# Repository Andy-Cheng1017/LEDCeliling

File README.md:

# LEDCeliling
 NTUT IXD Graduate Exhibition

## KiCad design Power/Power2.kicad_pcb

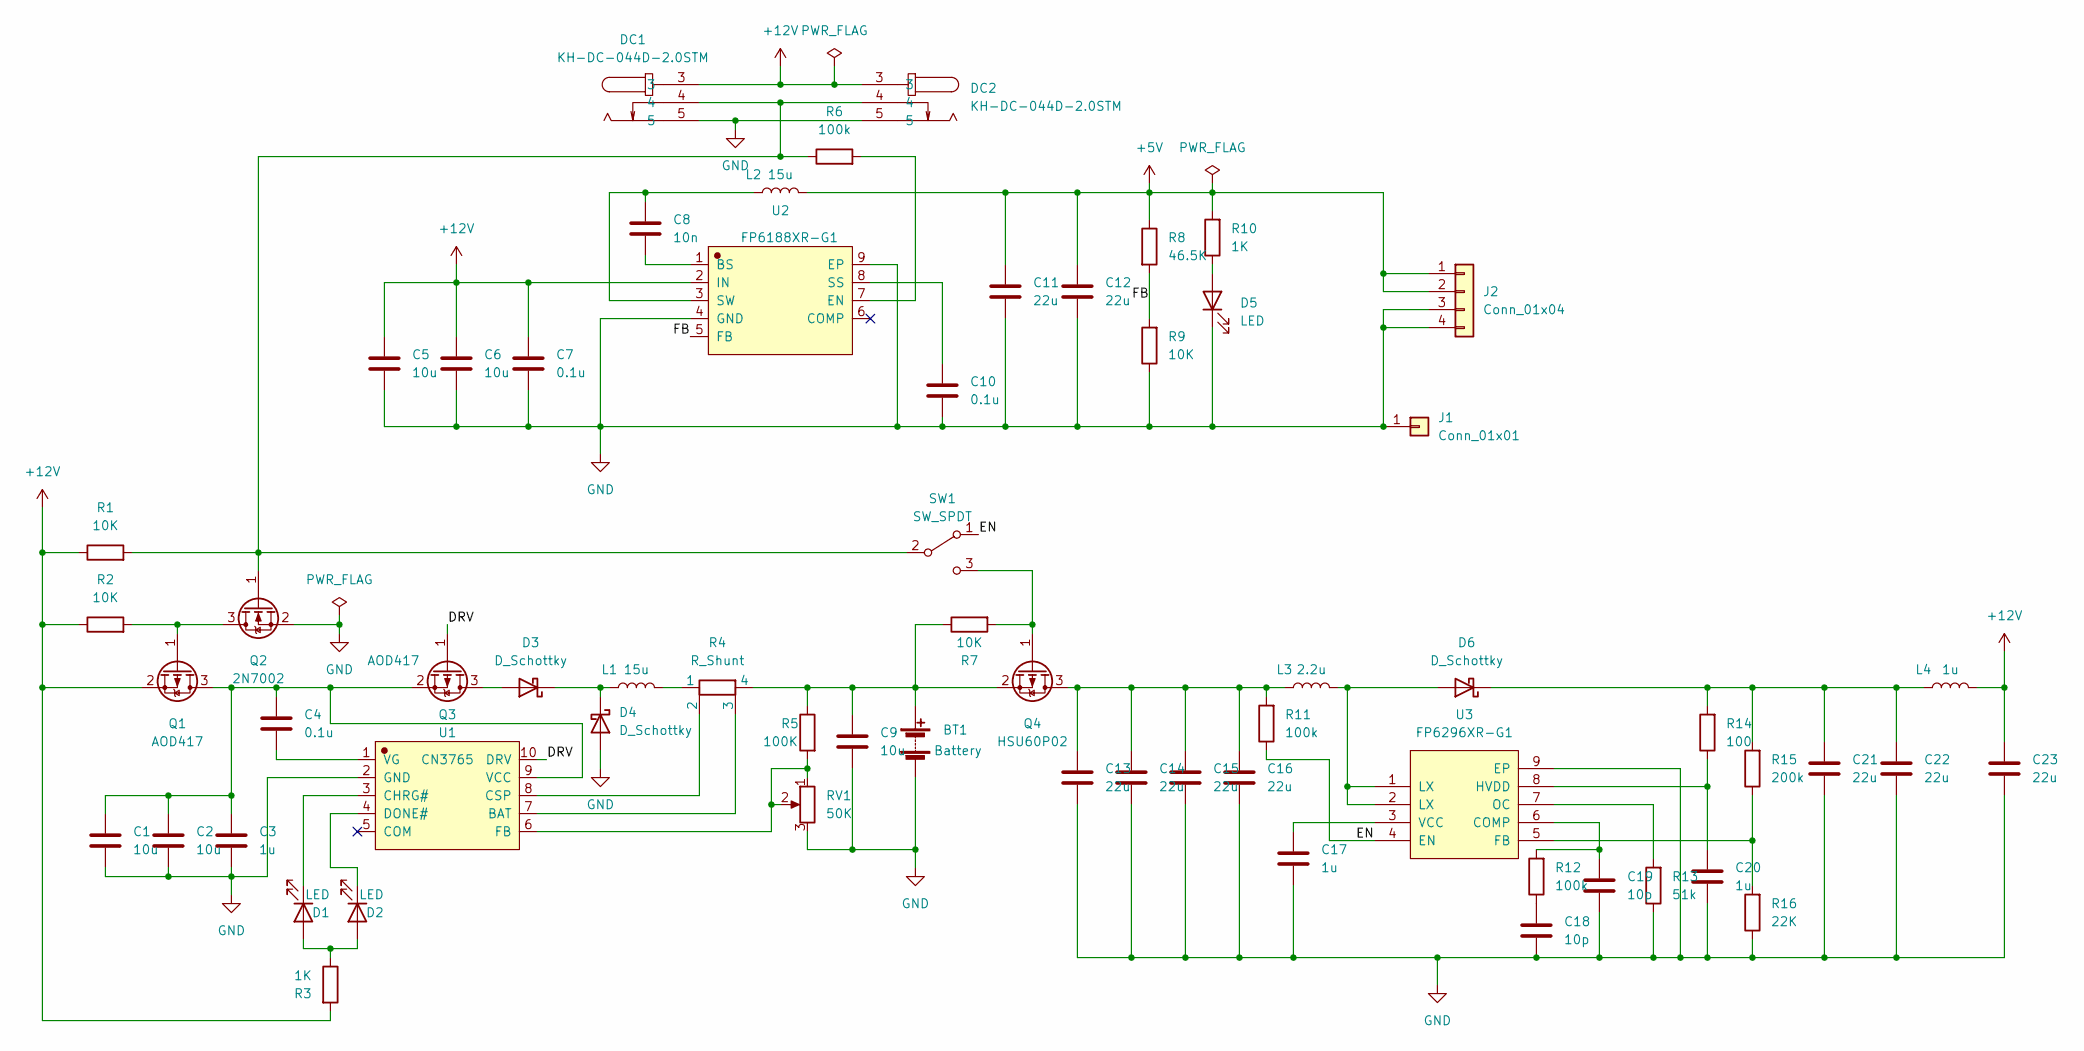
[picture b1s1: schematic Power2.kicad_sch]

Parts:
BT1: Battery
C1, C2, C5, C6, C9: 10u; C_0805_2012Metric
C3, C17, C20: 1u; C_0805_2012Metric
C4, C7, C10: 0.1u; C_0805_2012Metric
C8: 10n; C_0805_2012Metric
C11, C12, C13, C14, C15, C16, C21, C22, C23: 22u; C_0805_2012Metric
C18, C19: 10p; C_0805_2012Metric
D1, D2, D5: LED; LED_0805_2012Metric
D3, D4: D_Schottky; D_SMA
D6: D_Schottky; D_SMB
DC1, DC2: KH-DC-044D-2.0STM; DC-IN-TH_KH-DC-044D-2.0STM
J1: Conn_01x01; GndConnect
J2: Conn_01x04; VH3.96 4P SMT
L1, L2: 15u; IND-SMD_L7.5-W6.6
L3: 2.2u; IND-SMD_L7.5-W6.6
L4: 1u; L_1008_2520Metric
Q1, Q3: AOD417; TO-252-2
Q2: 2N7002; SOT-23
Q4: HSU60P02; TO-252-2
R1, R2, R7, R9: 10K; R_0805_2012Metric
R3, R10: 1K; R_0805_2012Metric
R4: R_Shunt; R_2512_6332Metric
R5: 100K; R_0805_2012Metric
R6, R11, R12: 100k; R_0805_2012Metric
R8: 46.5K; R_0805_2012Metric
R13: 51k; R_0805_2012Metric
R14: 100; R_0805_2012Metric
R15: 200k; R_0805_2012Metric
R16: 22K; R_0805_2012Metric
RV1: 50K; Potentiometer_Bourns_TC33X_Vertical
SW1: SW_SPDT; SW_SPDT_PCM12
U1: CN3765; SOIC-10_L4.9-W3.9-P1.00-LS6.0-BL
U2: FP6188XR-G1; SOIC-8-1EP_3.9x4.9mm_P1.27mm_EP2.95x4.9mm_Mask2.71x3.4mm_Th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
U3: FP6296XR-G1; SOIC-8-1EP_3.9x4.9mm_P1.27mm_EP2.95x4.9mm_Mask2.71x3.4mm_Th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

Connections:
+5V: C11.1, C12.1, J2.1, J2.2, L2.2, R8.1, R10.2
+12V: C5.1, C6.1, C7.1, C23.1, DC1.3, DC2.3, L4.2, Q1.2 (S), R1.1, R2.1, R3.2, U2.2 (IN)
/DRV: Q3.1 (G), U1.10 (DRV)
/EN: R11.1, SW1.1 (A), U3.4 (EN)
/FB: R8.2, R9.2, U2.5 (FB)
GND: BT1.2 (-), C1.2, C2.2, C3.2, C5.2, C6.2, C7.2, C9.2, C10.2, C11.2, C12.2, C13.2, C14.2, C15.2, C16.2, C17.2, C18.2, C19.2, C20.2, C21.2, C22.2, C23.2, D4.2 (A), D5.1 (K), DC1.5, DC2.5, J1.1, J2.3, J2.4, Q2.2 (S), R9.1, R13.1, R16.1, RV1.3, U1.2 (GND), U2.4 (GND), U2.9 (EP), U3.9 (EP)
unnamed: BT1.1 (+), C9.1, Q4.2 (S), R4.4, R5.1, R7.1
unnamed: C1.1, C2.1, C3.1, C4.1, Q1.3 (D), Q3.2 (S), U1.9 (VCC)
unnamed: C4.2, U1.1 (VG)
unnamed: C8.1, U2.1 (BS)
unnamed: C8.2, L2.1, U2.3 (SW)
unnamed: C10.1, U2.8 (SS)
unnamed: C13.1, C14.1, C15.1, C16.1, L3.1, Q4.3 (D), R11.2
unnamed: C17.1, U3.3 (VCC)
unnamed: C18.1, R12.1
unnamed: C19.1, R12.2, U3.6 (COMP)
unnamed: C20.1, R14.1, U3.8 (HVDD)
unnamed: C21.1, C22.1, D6.1 (K), L4.1, R14.2, R15.2
unnamed: D1.1 (K), U1.3 (CHRG#)
unnamed: D1.2 (A), D2.2 (A), R3.1
unnamed: D2.1 (K), U1.4 (DONE#)
unnamed: D3.1 (K), D4.1 (K), L1.1
unnamed: D3.2 (A), Q3.3 (D)
unnamed: D5.2 (A), R10.1
unnamed: D6.2 (A), L3.2, U3.1 (LX), U3.2 (LX)
unnamed: DC1.4, DC2.4, Q2.1 (G), R1.2, R6.1, SW1.2 (B)
unnamed: L1.2, R4.1
unnamed: Q1.1 (G), Q2.3 (D), R2.2
unnamed: Q4.1 (G), R7.2, SW1.3 (C)
unnamed: R4.2, U1.8 (CSP)
unnamed: R4.3, U1.7 (BAT)
unnamed: R5.2, RV1.1, RV1.2, U1.6 (FB)
unnamed: R6.2, U2.7 (EN)
unnamed: R13.2, U3.7 (OC)
unnamed: R15.1, R16.2, U3.5 (FB)

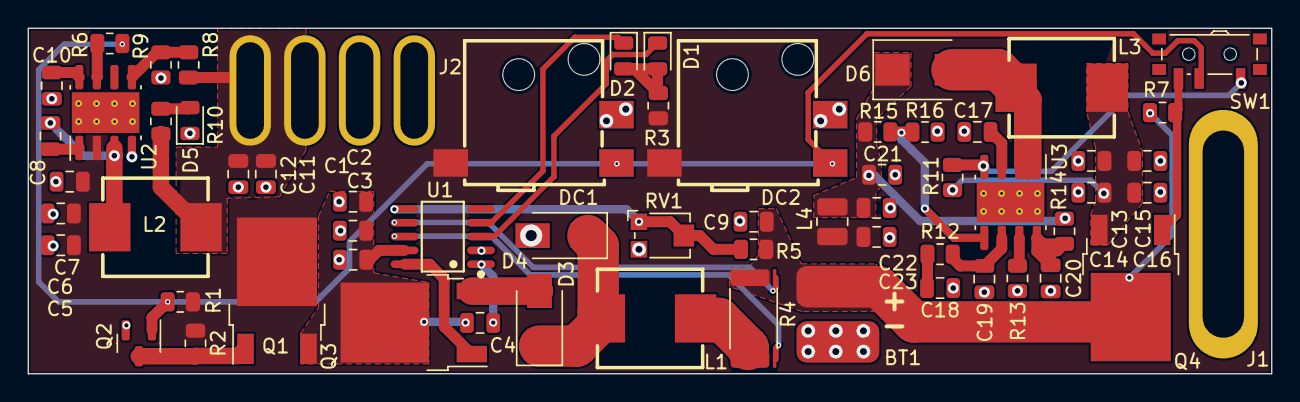
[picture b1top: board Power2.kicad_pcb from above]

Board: 2 copper layers, 90.0 x 25.0 mm, 63 parts (0 on the bottom side), 35 nets.

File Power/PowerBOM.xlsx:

Comment | Designator | Footprint | JLCPCB Part
10u | C1, C2, C5, C6, C9, | Capacitor_SMD:C_0805_2012Metric | C15850
1u | C3, C17, C20, | Capacitor_SMD:C_0805_2012Metric | C2798196
0.1u | C4, C7, C10, | Capacitor_SMD:C_0805_2012Metric | C282732
10n | C8, | Capacitor_SMD:C_0805_2012Metric | C376921
22u | C11, C12, C13, C14, C15, C16, C21, C22, C23, | Capacitor_SMD:C_0805_2012Metric | C45783
10p | C18, C19, | Capacitor_SMD:C_0805_2012Metric | C344177
LED | D1, D5, | LED_SMD:LED_0805_2012Metric | C965812
LED | D2 | LED_SMD:LED_0805_2012Metric | C965816
D_Schottky | D3, D4, | Diode_SMD:D_SMA | C3018536
D_Schottky | D6, | Diode_SMD:D_SMB | C2903947
KH-DC-044D-2.0STM | DC1, DC2, | 1component:DC-044D-2.5A-2.5-SMT | C397343
15u | L1, L2, | 1component:IND-SMD_L7.5-W6.6 | C3002651
2.2u | L3, | 1component:IND-SMD_L7.5-W6.6 | C3002634
1u | L4, | Inductor_SMD:L_1008_2520Metric | C2044935
AOD417 | Q1, Q3, | Package_TO_SOT_SMD:TO-252-2 | C4748754
2N7002 | Q2, | Package_TO_SOT_SMD:SOT-23 | C3008370
HSU60P02 | Q4, | Package_TO_SOT_SMD:TO-252-2 | C845610
10K | R1, R2, R7, R9, | Resistor_SMD:R_0805_2012Metric | C3152217
1K | R3, R10, | Resistor_SMD:R_0805_2012Metric | C17414
100k | R5, R6, R11, R12, | Resistor_SMD:R_0805_2012Metric | C149504
46.5K | R8, | Resistor_SMD:R_0805_2012Metric | C17704
51k | R13, | Resistor_SMD:R_0805_2012Metric | C5356361
100 | R14, | Resistor_SMD:R_0805_2012Metric | C25277
200k | R15, | Resistor_SMD:R_0805_2012Metric | C5356338
22K | R16, | Resistor_SMD:R_0805_2012Metric | C5140879
50K | RV1, | 1component:Potentiometer_Bourns_TC33X_Vertical | C145161
SW_SPDT | SW1, | Button_Switch_SMD:SW_SPDT_PCM12 | C431540
CN3765 | U1, | 1component:SOIC-10_L4.9-W3.9-P1.00-LS6.0-BL | C41308
FP6188XR-G1 | U2, | 1component:SOIC-8-1EP_3.9x4.9mm_P1.27mm_EP2.95x4.9mm_Mask2.71x3.4mm_ThermalVias | C114311
FP6296XR-G1 | U3, | 1component:SOIC-8-1EP_3.9x4.9mm_P1.27mm_EP2.95x4.9mm_Mask2.71x3.4mm_ThermalVias | C133888

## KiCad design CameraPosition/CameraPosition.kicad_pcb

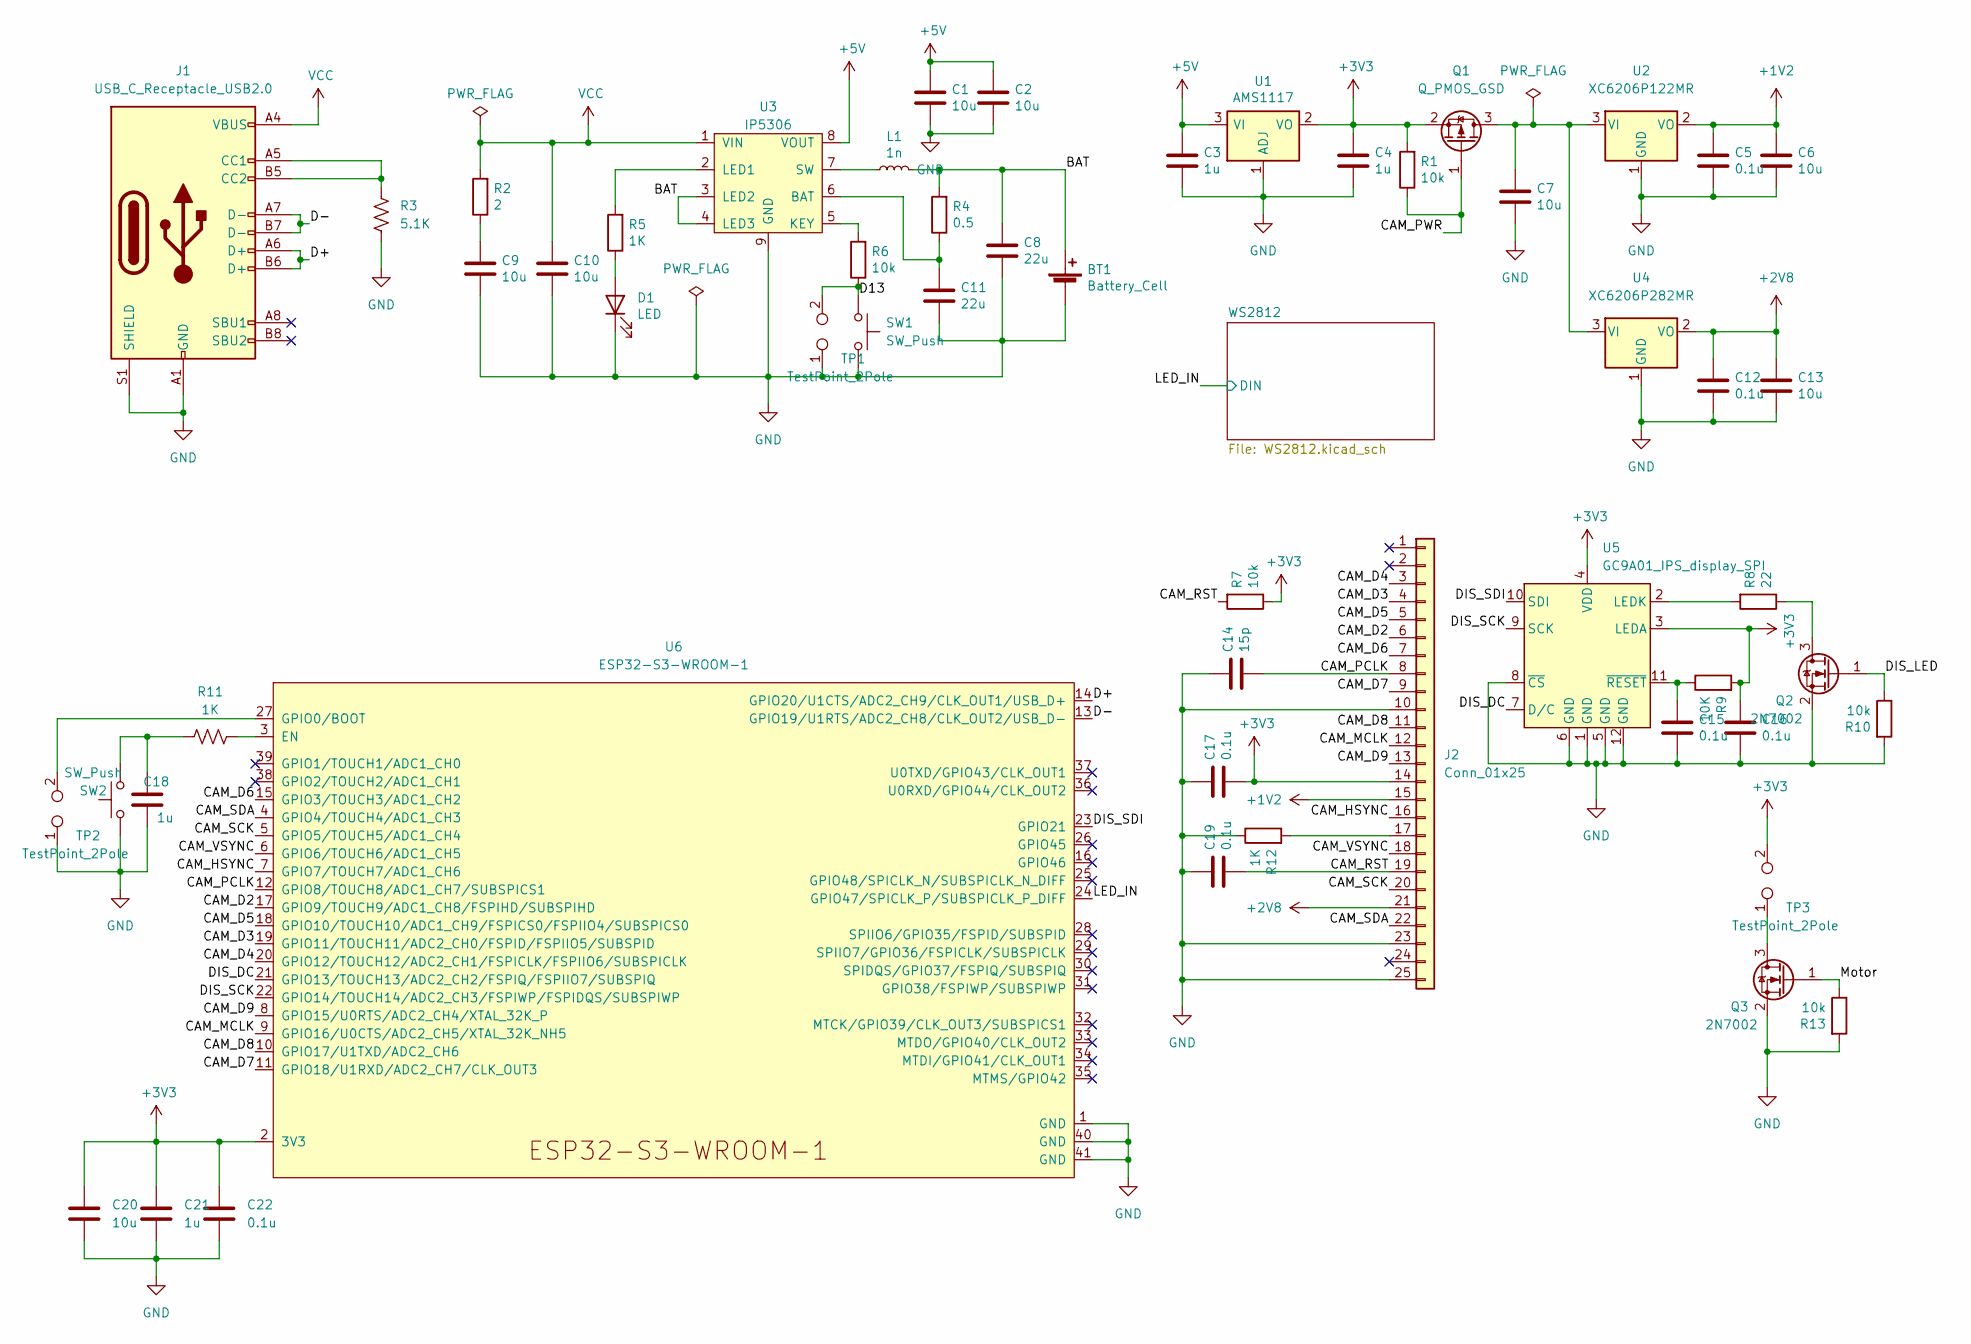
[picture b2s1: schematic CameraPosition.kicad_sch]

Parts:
BT1: Battery_Cell; PinHeader_1x02_P2.54mm_Vertical
C1, C2, C6, C7, C9, C10, C13, C20: 10u; C_0805_2012Metric
C3, C4, C18, C21: 1u; C_0805_2012Metric
C5, C12, C15, C16, C17, C19, C22: 0.1u; C_0805_2012Metric
C8, C11: 22u; C_0805_2012Metric
C14: 15p; C_0805_2012Metric
D1: LED; LED_0805_2012Metric
J1: USB_C_Receptacle_USB2.0; USB_C_Receptacle_HRO_TYPE-C-31-M-12
J2: Conn_01x25; Hirose_FH12-24S-0.5SH_1x24-1MP_P0.50mm_Horizontal
L1: 1n; L_Wuerth_MAPI-2512
Q1: Q_PMOS_GSD; SOT-23
Q2, Q3: 2N7002; SOT-23
R1, R6, R7, R10, R13: 10k; R_0805_2012Metric
R2: 2; R_0805_2012Metric
R3: 5.1K; R_0805_2012Metric
R4: 0.5; R_0805_2012Metric
R5, R11, R12: 1K; R_0805_2012Metric
R8: 22; R_0805_2012Metric
R9: 10K; R_0805_2012Metric
SW1, SW2: SW_Push; SW_SPST_CK_RS282G05A3
TP1, TP2, TP3: TestPoint_2Pole; PinHeader_1x02_P2.00mm_Vertical
U1: AMS1117; SOT-223-3_TabPin2
U2: XC6206P122MR; SOT-23
U3: IP5306; SOIC-8-1EP_3.9x4.9mm_P1.27mm_EP2.29x3mm
U4: XC6206P282MR; SOT-23
U5: GC9A01_IPS_display_SPI; GC9A01_IPS_display
U6: ESP32-S3-WROOM-1; ESP32-S3-WROOM-1U

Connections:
+1V2: C5.2, C6.2, J2.15, U2.2 (VO)
+2V8: C12.2, C13.2, J2.21, U4.2 (VO)
+3V3: C4.2, C16.2, C17.1, C20.1, C21.1, C22.1, J2.14, Q1.2 (S), R1.2, R7.1, R9.2, TP3.2, U1.2 (VO), U5.3 (LEDA), U5.4 (VDD), U6.2 (3V3)
+5V: C1.2, C2.2, C3.2, U1.3 (VI), U3.8 (VOUT); also elsewhere on the board
/BAT: BT1.1 (+), C8.2, L1.2, R4.2, U3.3 (LED2), U3.4 (LED3)
/CAM_D2: J2.6, U6.17 (GPIO9/TOUCH9/ADC1_CH8/FSPIHD/SUBSPIHD)
/CAM_D3: J2.4, U6.19 (GPIO11/TOUCH11/ADC2_CH0/FSPID/FSPIIO5/S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)
/CAM_D4: J2.3, U6.20 (GPIO12/TOUCH12/ADC2_CH1/FSPICLK/FSPIIO6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)
/CAM_D5: J2.5, U6.18 (GPIO10/TOUCH10/ADC1_CH9/FSPICS0/FSPIIO4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)
/CAM_D6: J2.7, U6.15 (GPIO3/TOUCH3/ADC1_CH2)
/CAM_D7: J2.9, U6.11 (GPIO18/U1RXD/ADC2_CH7/CLK_OUT3)
/CAM_D8: J2.11, U6.10 (GPIO17/U1TXD/ADC2_CH6)
/CAM_D9: J2.13, U6.8 (GPIO15/U0RTS/ADC2_CH4/XTAL_32K_P)
/CAM_HSYNC: J2.16, U6.7 (GPIO7/TOUCH7/ADC1_CH6)
/CAM_MCLK: J2.12, U6.9 (GPIO16/U0CTS/ADC2_CH5/XTAL_32K_NH5)
/CAM_PCLK: C14.1, J2.8, U6.12 (GPIO8/TOUCH8/ADC1_CH7/SUBSPICS1)
/CAM_PWR: Q1.1 (G), R1.1
/CAM_RST: C19.1, J2.19, R7.2
/CAM_SCK: J2.20, U6.5 (GPIO5/TOUCH5/ADC1_CH4)
/CAM_SDA: J2.22, U6.4 (GPIO4/TOUCH4/ADC1_CH3)
/CAM_VSYNC: J2.18, U6.6 (GPIO6/TOUCH6/ADC1_CH5)
/D13: R6.1, SW1.1, TP1.2
/D+: J1.A6 (D+), J1.B6 (D+), U6.14 (GPIO20/U1CTS/ADC2_CH9/CLK_OUT1/USB_D+)
/D-: J1.A7 (D-), J1.B7 (D-), U6.13 (GPIO19/U1RTS/ADC2_CH8/CLK_OUT2/USB_D-)
/DIS_DC: U5.7 (D/C), U6.21 (GPIO13/TOUCH13/ADC2_CH2/FSPIQ/FSPIIO7/S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)
/DIS_LED: Q2.1 (G), R10.1
/DIS_SCK: U5.9 (SCK), U6.22 (GPIO14/TOUCH14/ADC2_CH3/FSPIWP/FSPIDQS/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)
/DIS_SDI: U5.10 (SDI), U6.23 (GPIO21)
/LED_IN: U6.24 (GPIO47/SPICLK_P/SUBSPICLK_P_DIFF); also elsewhere on the board
/Motor: Q3.1 (G), R13.1
GND: BT1.2 (-), C1.1, C2.1, C3.1, C4.1, C5.1, C6.1, C7.1, C8.1, C9.1, C10.1, C11.1, C12.1, C13.1, C14.2, C15.1, C16.1, C17.2, C18.1, C19.2, C20.2, C21.2, C22.2, D1.1 (K), J1.A1 (GND), J1.A12 (GND), J1.B1 (GND), J1.B12 (GND), J1.S1 (SHIELD), J2.10, J2.23, J2.25, Q2.2 (S), Q3.2 (S), R3.2, R10.2, R12.1, R13.2, SW1.2, SW2.1, TP1.1, TP2.1, U1.1 (ADJ), U2.1 (GND), U3.9 (GND), U4.1 (GND), U5.1 (GND), U5.5 (GND), U5.6 (GND), U5.8 (~CS), U5.12 (GND), U6.1 (GND), U6.40 (GND), U6.41 (GND); also elsewhere on the board
unnamed: C7.2, Q1.3 (D), U2.3 (VI), U4.3 (VI)
unnamed: C9.2, R2.1
unnamed: C11.2, R4.1, U3.6 (BAT)
unnamed: C15.2, R9.1, U5.11 (~RESET)
unnamed: C18.2, R11.1, SW2.2
unnamed: D1.2 (A), R5.1
unnamed: J1.A5 (CC1), J1.B5 (CC2), R3.1
unnamed: J2.17, R12.2
unnamed: L1.1, U3.7 (SW)
unnamed: Q2.3 (D), R8.1
unnamed: Q3.3 (D), TP3.1
unnamed: R5.2, U3.2 (LED1)
unnamed: R6.2, U3.5 (KEY)
unnamed: R8.2, U5.2 (LEDK)
unnamed: R11.2, U6.3 (EN)
unnamed: TP2.2, U6.27 (GPIO0/BOOT)
VCC: C10.2, J1.A4 (VBUS), J1.A9 (VBUS), J1.B4 (VBUS), J1.B9 (VBUS), R2.2, U3.1 (VIN)

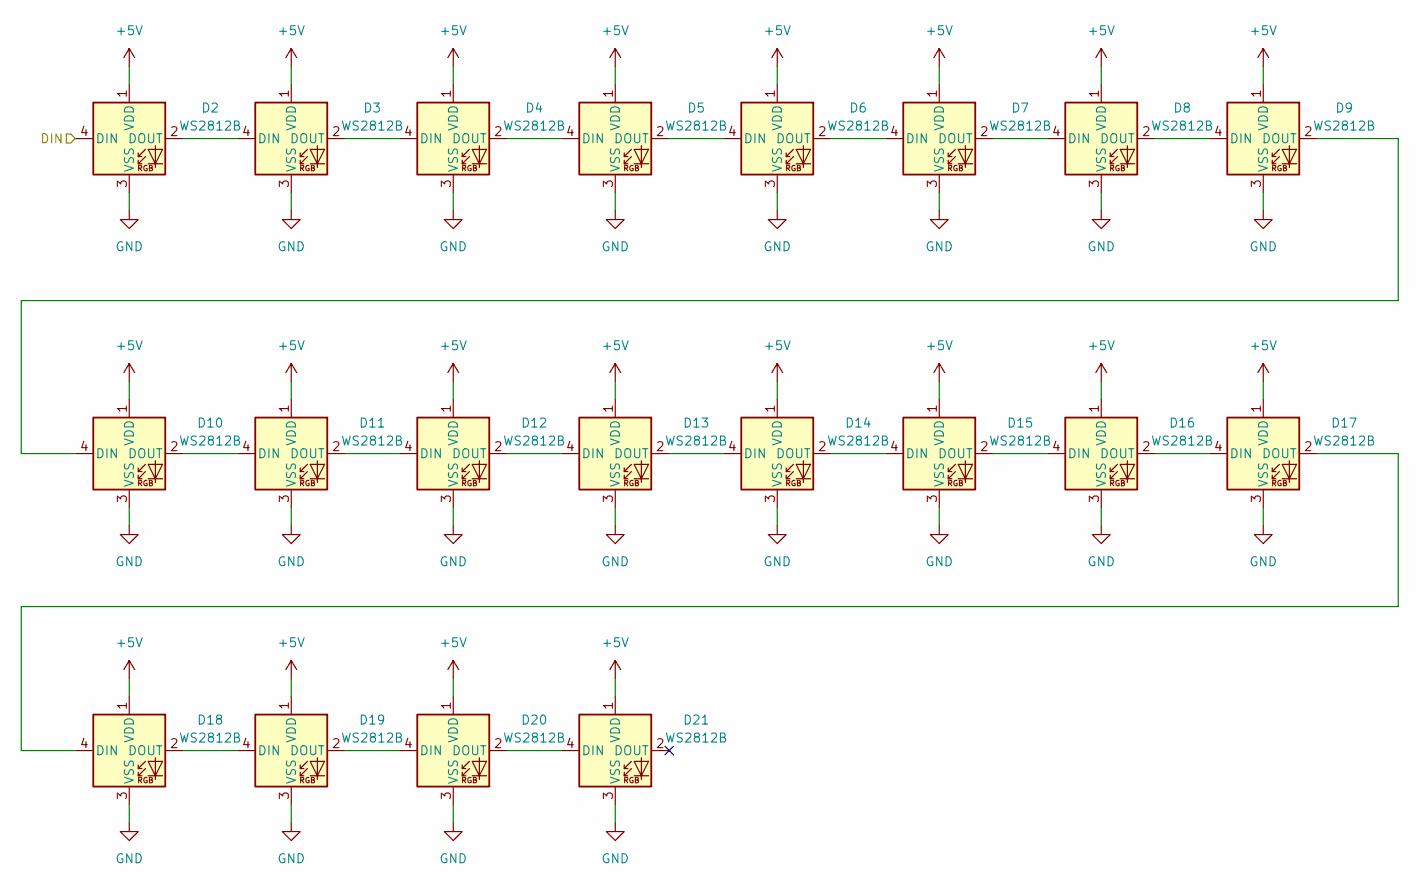
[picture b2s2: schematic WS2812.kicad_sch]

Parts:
D2, D3, D4, D5, D6, D7, D8, D9, D10, D11, D12, D13, D14, D15, D16, D17, D18, D19, D20, D21: WS2812B; LED_WS2812B_PLCC4_5.0x5.0mm_P3.2mm

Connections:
+5V: D2.1 (VDD), D3.1 (VDD), D4.1 (VDD), D5.1 (VDD), D6.1 (VDD), D7.1 (VDD), D8.1 (VDD), D9.1 (VDD), D10.1 (VDD), D11.1 (VDD), D12.1 (VDD), D13.1 (VDD), D14.1 (VDD), D15.1 (VDD), D16.1 (VDD), D17.1 (VDD), D18.1 (VDD), D19.1 (VDD), D20.1 (VDD), D21.1 (VDD); also elsewhere on the board
/LED_IN: D2.4 (DIN); also elsewhere on the board
GND: D2.3 (VSS), D3.3 (VSS), D4.3 (VSS), D5.3 (VSS), D6.3 (VSS), D7.3 (VSS), D8.3 (VSS), D9.3 (VSS), D10.3 (VSS), D11.3 (VSS), D12.3 (VSS), D13.3 (VSS), D14.3 (VSS), D15.3 (VSS), D16.3 (VSS), D17.3 (VSS), D18.3 (VSS), D19.3 (VSS), D20.3 (VSS), D21.3 (VSS); also elsewhere on the board
unnamed: D2.2 (DOUT), D3.4 (DIN)
unnamed: D3.2 (DOUT), D4.4 (DIN)
unnamed: D4.2 (DOUT), D5.4 (DIN)
unnamed: D5.2 (DOUT), D6.4 (DIN)
unnamed: D6.2 (DOUT), D7.4 (DIN)
unnamed: D7.2 (DOUT), D8.4 (DIN)
unnamed: D8.2 (DOUT), D9.4 (DIN)
unnamed: D10.2 (DOUT), D11.4 (DIN)
unnamed: D9.2 (DOUT), D10.4 (DIN)
unnamed: D11.2 (DOUT), D12.4 (DIN)
unnamed: D12.2 (DOUT), D13.4 (DIN)
unnamed: D13.2 (DOUT), D14.4 (DIN)
unnamed: D14.2 (DOUT), D15.4 (DIN)
unnamed: D15.2 (DOUT), D16.4 (DIN)
unnamed: D16.2 (DOUT), D17.4 (DIN)
unnamed: D17.2 (DOUT), D18.4 (DIN)
unnamed: D18.2 (DOUT), D19.4 (DIN)
unnamed: D19.2 (DOUT), D20.4 (DIN)
unnamed: D20.2 (DOUT), D21.4 (DIN)

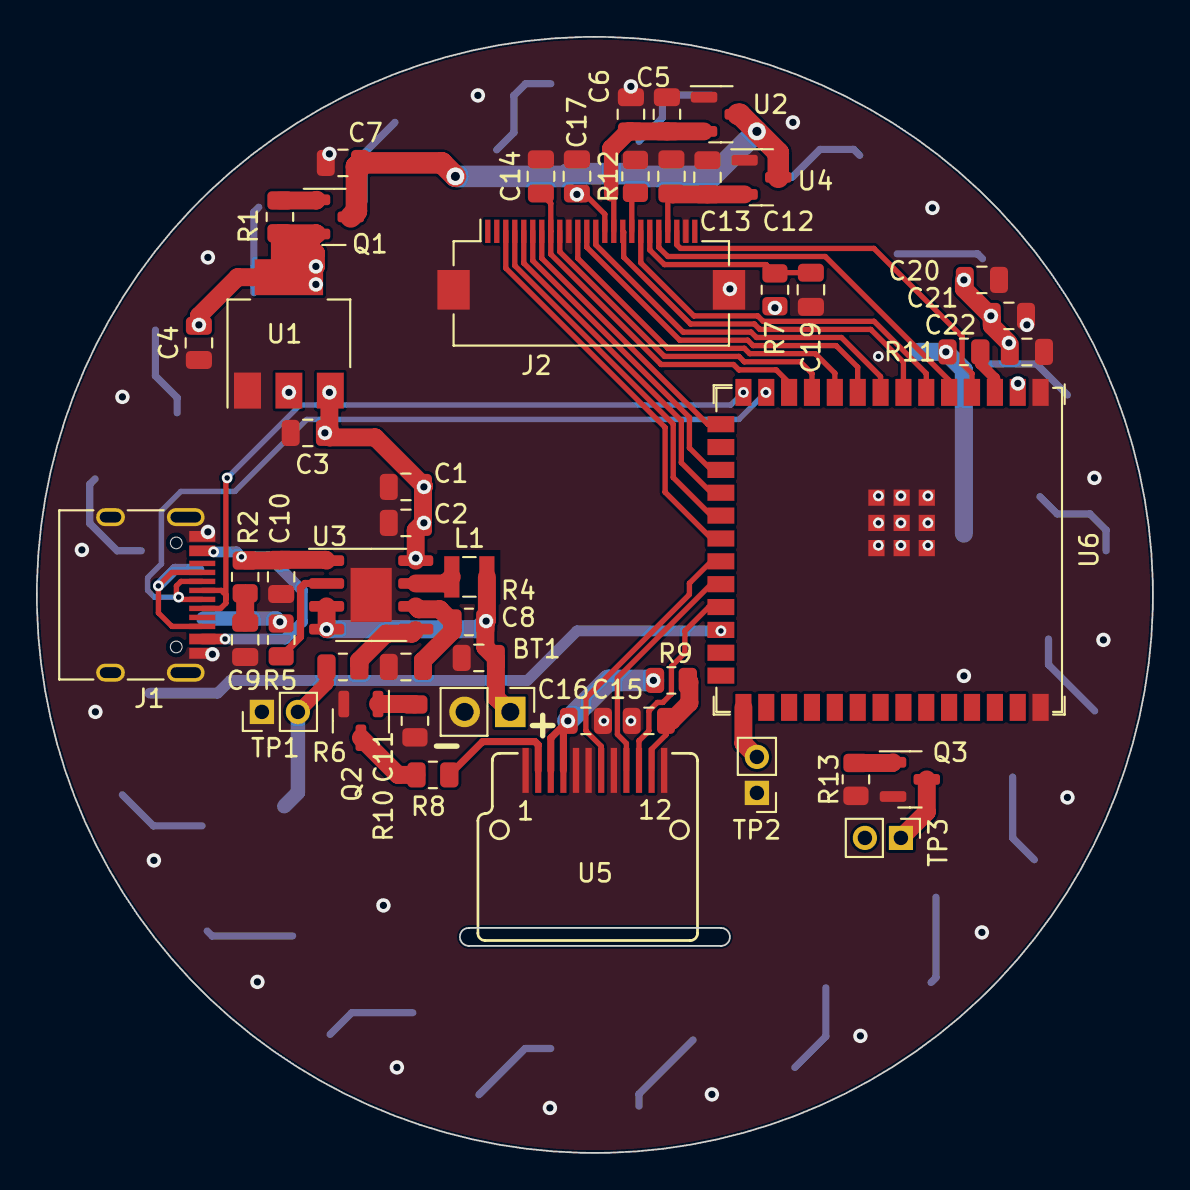
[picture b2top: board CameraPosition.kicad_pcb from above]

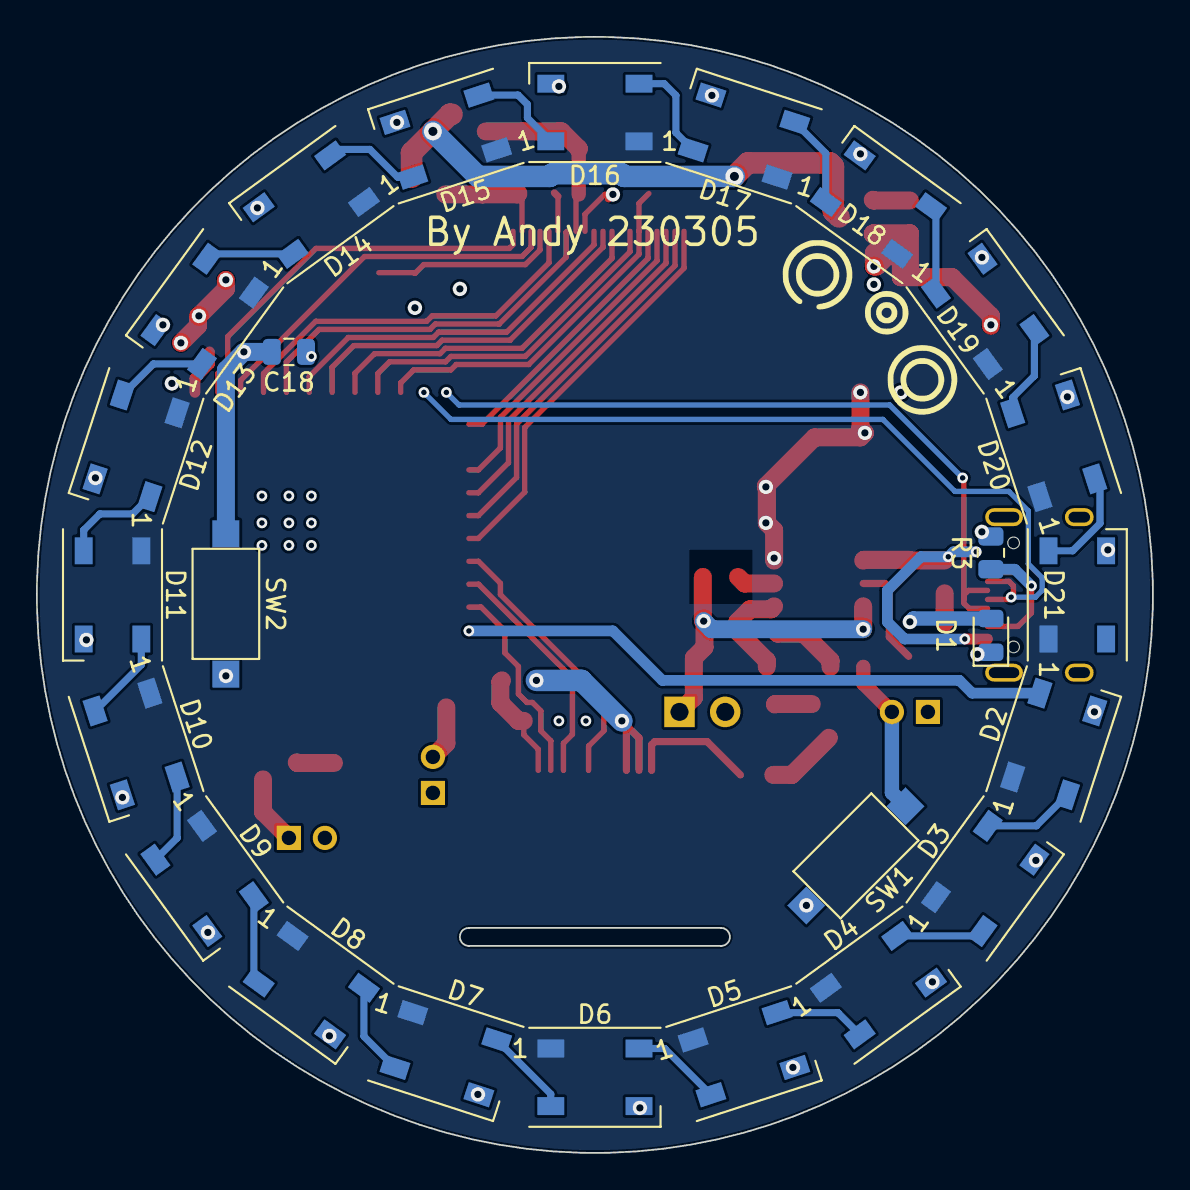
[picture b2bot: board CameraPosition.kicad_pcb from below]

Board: 4 copper layers, 62.0 x 62.0 mm, 74 parts (25 on the bottom side), 67 nets.

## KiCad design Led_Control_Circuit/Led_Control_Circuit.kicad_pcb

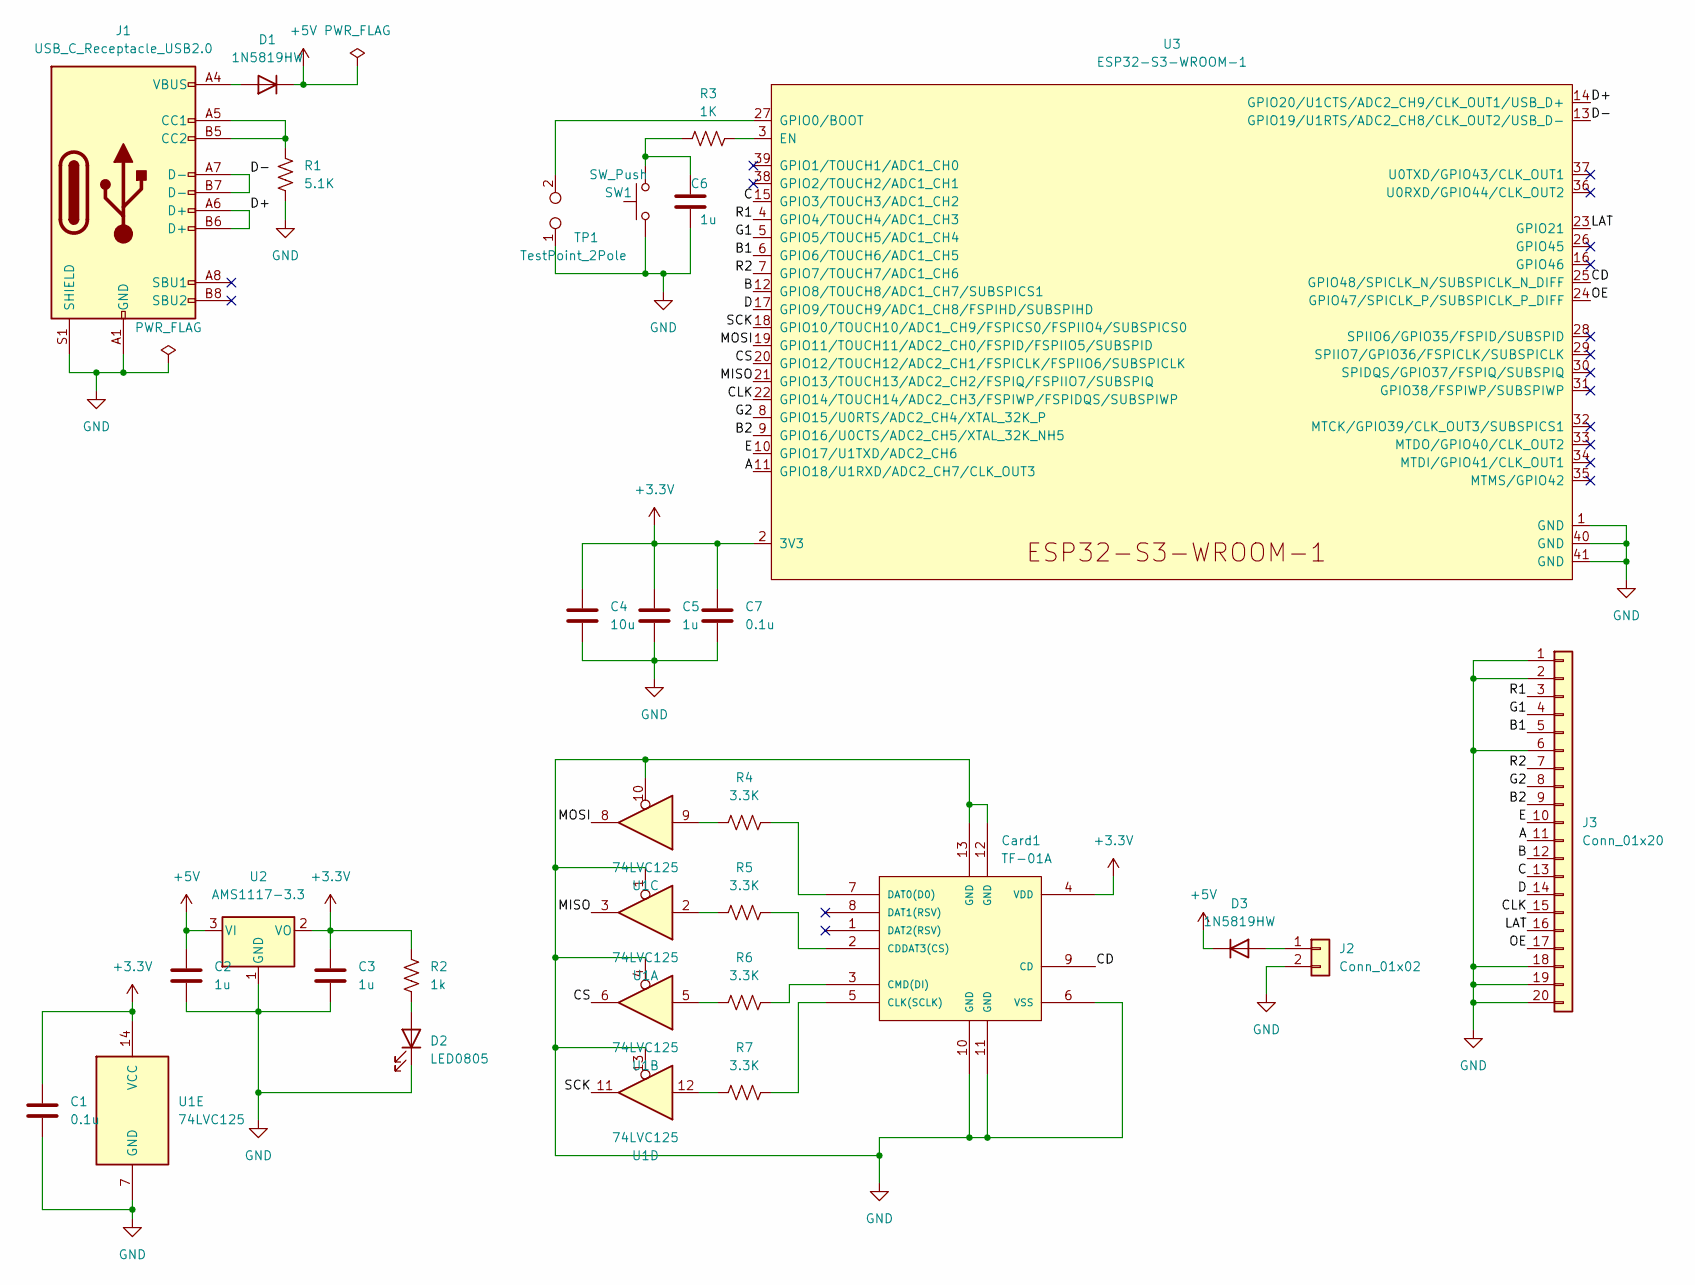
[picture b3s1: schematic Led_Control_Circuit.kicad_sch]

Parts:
C1, C7: 0.1u; C_0805_2012Metric
C2, C3, C5, C6: 1u; C_0805_2012Metric
C4: 10u; C_0805_2012Metric
Card1: TF-01A; TF-SMD_TF-01A
D1, D3: 1N5819HW; D_SOD-123
D2: LED0805; LED_0805_2012Metric
J1: USB_C_Receptacle_USB2.0; USB_C_Receptacle_HRO_TYPE-C-31-M-12
J2: Conn_01x02; Battery
J3: Conn_01x20; PinSocket_2x10_P2.54mm_Vertical_SMD
R1: 5.1K; R_0805_2012Metric
R2: 1k; R_0805_2012Metric
R3: 1K; R_0805_2012Metric
R4, R5, R6, R7: 3.3K; R_0805_2012Metric
SW1: SW_Push; SW_SPST_CK_RS282G05A3
TP1: TestPoint_2Pole; PinHeader_1x02_P2.00mm_Vertical
U1: 74LVC125; TSSOP-14_4.4x5mm_P0.65mm
U2: AMS1117-3.3; SOT-223-3_TabPin2
U3: ESP32-S3-WROOM-1; ESP32-S3-WROOM-1U

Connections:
+3.3V: C1.1, C3.1, C4.1, C5.1, C7.1, Card1.4 (VDD), R2.2, U1.14 (VCC), U2.2 (VO), U3.2 (3V3)
+5V: C2.1, D1.1 (K), D3.1 (K), U2.3 (VI)
/A: J3.11, U3.11 (GPIO18/U1RXD/ADC2_CH7/CLK_OUT3)
/B: J3.12, U3.12 (GPIO8/TOUCH8/ADC1_CH7/SUBSPICS1)
/B1: J3.5, U3.6 (GPIO6/TOUCH6/ADC1_CH5)
/B2: J3.9, U3.9 (GPIO16/U0CTS/ADC2_CH5/XTAL_32K_NH5)
/C: J3.13, U3.15 (GPIO3/TOUCH3/ADC1_CH2)
/CD: Card1.9 (CD), U3.25 (GPIO48/SPICLK_N/SUBSPICLK_N_DIFF)
/CLK: J3.15, U3.22 (GPIO14/TOUCH14/ADC2_CH3/FSPIWP/FSPIDQS/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)
/CS: U1.6, U3.20 (GPIO12/TOUCH12/ADC2_CH1/FSPICLK/FSPIIO6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)
/D: J3.14, U3.17 (GPIO9/TOUCH9/ADC1_CH8/FSPIHD/SUBSPIHD)
/D+: J1.A6 (D+), J1.B6 (D+), U3.14 (GPIO20/U1CTS/ADC2_CH9/CLK_OUT1/USB_D+)
/D-: J1.A7 (D-), J1.B7 (D-), U3.13 (GPIO19/U1RTS/ADC2_CH8/CLK_OUT2/USB_D-)
/E: J3.10, U3.10 (GPIO17/U1TXD/ADC2_CH6)
/G1: J3.4, U3.5 (GPIO5/TOUCH5/ADC1_CH4)
/G2: J3.8, U3.8 (GPIO15/U0RTS/ADC2_CH4/XTAL_32K_P)
/LAT: J3.16, U3.23 (GPIO21)
/MISO: U1.3, U3.21 (GPIO13/TOUCH13/ADC2_CH2/FSPIQ/FSPIIO7/S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)
/MOSI: U1.8, U3.19 (GPIO11/TOUCH11/ADC2_CH0/FSPID/FSPIIO5/S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)
/OE: J3.17, U3.24 (GPIO47/SPICLK_P/SUBSPICLK_P_DIFF)
/R1: J3.3, U3.4 (GPIO4/TOUCH4/ADC1_CH3)
/R2: J3.7, U3.7 (GPIO7/TOUCH7/ADC1_CH6)
/SCK: U1.11, U3.18 (GPIO10/TOUCH10/ADC1_CH9/FSPICS0/FSPIIO4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)
GND: C1.2, C2.2, C3.2, C4.2, C5.2, C6.1, C7.2, Card1.6 (VSS), Card1.10 (GND), Card1.11 (GND), Card1.12 (GND), Card1.13 (GND), D2.1 (K), J1.A1 (GND), J1.A12 (GND), J1.B1 (GND), J1.B12 (GND), J1.S1 (SHIELD), J2.2, J3.1, J3.2, J3.6, J3.18, J3.19, J3.20, R1.2, SW1.1, TP1.1, U1.1, U1.4, U1.7 (GND), U1.10, U1.13, U2.1 (GND), U3.1 (GND), U3.40 (GND), U3.41 (GND)
unnamed: C6.2, R3.1, SW1.2
unnamed: Card1.2 (CDDAT3(CS)), R5.1
unnamed: Card1.3 (CMD(DI)), R6.1
unnamed: Card1.5 (CLK(SCLK)), R7.1
unnamed: Card1.7 (DAT0(D0)), R4.1
unnamed: D1.2 (A), J1.A4 (VBUS), J1.A9 (VBUS), J1.B4 (VBUS), J1.B9 (VBUS)
unnamed: D2.2 (A), R2.1
unnamed: D3.2 (A), J2.1
unnamed: J1.A5 (CC1), J1.B5 (CC2), R1.1
unnamed: R3.2, U3.3 (EN)
unnamed: R4.2, U1.9
unnamed: R5.2, U1.2
unnamed: R6.2, U1.5
unnamed: R7.2, U1.12
unnamed: TP1.2, U3.27 (GPIO0/BOOT)

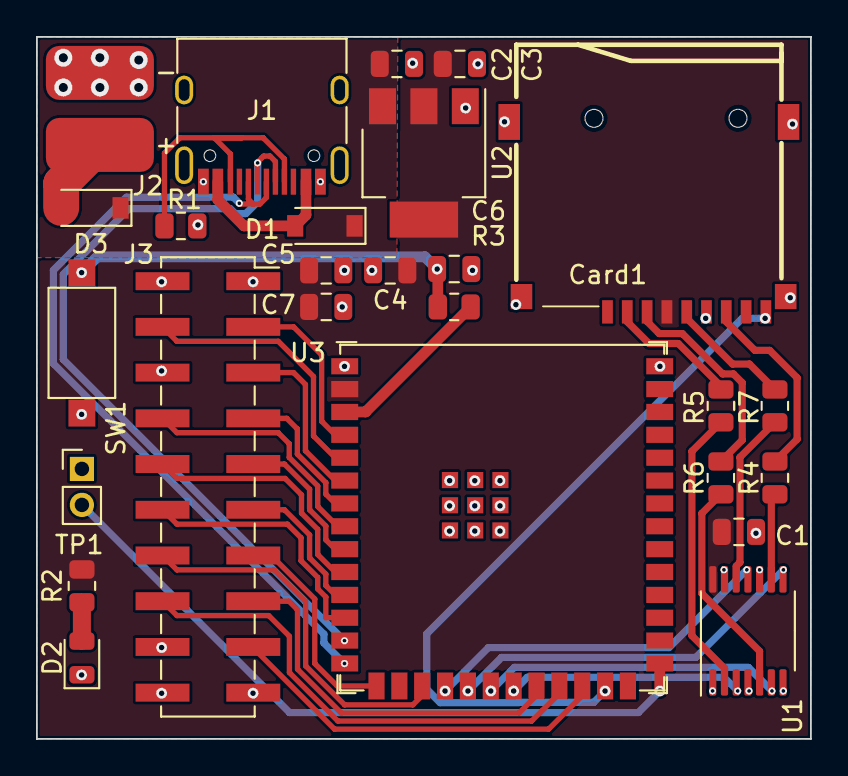
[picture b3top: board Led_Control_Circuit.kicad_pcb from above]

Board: 2 copper layers, 43.0 x 39.0 mm, 26 parts (0 on the bottom side), 39 nets.
